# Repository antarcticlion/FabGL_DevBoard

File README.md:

# FabGL_DevBoard
 FabGL development board using ESP32-DevkitC-V4

---

解説は後で書きます。

---

---
# Lastest gerber

https://github.com/antarcticlion/FabGL_DevBoard/raw/main/FabGL_SBC/gerber/ESP32DevkitC-V4-SBC-FabGL_02.zip

---
# BOM

|番号|部品|数|
|:---|:---|:---|
| J1,J2 | ミニＤＩＮソケットfemale 6p | 2|
| J3 | マイクロSDソケット ヒロセDM3AT-SF-PEJM5 | 1|
| U1 | 1x19 ピンソケット | 2|
| U1 | ESP32-DebkitC-VE (Insert to pinsocket) | 1|
| R1～R4 | 2KR抵抗 7mm スルーホール | 4|
| R5～R8,R15,R26,R30 | 120R抵抗 7mm スルーホール | 7|
| R22 | 10KR抵抗 7mm スルーホール | 1|
| R34 | 470R抵抗 7mm スルーホール | 1|
| R9～R14,R16～R21,R23～R25,R27～R29 | 200R抵抗 7mm スルーホール | 18|
| J6 | DE15 Dsub-15P 3rows female horizontal pcb | 1|
| J5 | 3.5mmステレオミニジャック MJ-495A | 1|
| D1 | 5mm LED | 1|
| C2 | 10uF 2.5mm pitch MLCC | 1|
| C1,C10 | 0.1uF 5mm pitch MLCC | 2|
| C8 | 0.33uF 5mm pitch MLCC | 1|
| SW1 or SW2 | SPDT togle switch | 1|
| U7 | STMicroelectronics L7805CV | 1|
| J11 | DC Barreljack | 1|

---
# 取り扱いの注意点
・USBから給電するときはDCジャックの給電を止めてください。  
・ファームウェア更新時にはBootボタンを押す必要があります。Arduino IDE から「→」ボタンで転送を始めたら、しばらく待った後で"Connecting...."と表示された後ですぐbootボタンを押して、転送が開始されたら放してください。  
・I2Cは未チェックです。  
・ESP32-WROVERに対応するためピンアウトを一部変えています。SDカードやエキスパンダを使う場合、初期化時にピン番号を指定してください。  
| 信号 | ピン |
|:---|:---|
| MISO | 35 |
| MOSI | 12 |
| SCK | 14 |
| SS | 13 |

---

# Related Links

https://github.com/fdivitto/FabGL

---

# LICENCE
  
Copyright Antarcticlion 2022. This source describes Open Hardware and is licensed under the CERN-OHLW v2  
  
You may redistribute and modify this documentation and make products using it under the terms of the CERN-OHL-W v2 (https:/cern.ch/cern-ohl). This documentation is distributed WITHOUT ANY EXPRESS OR IMPLIED WARRANTY, INCLUDING OF MERCHANTABILITY, SATISFACTORY QUALITY AND FITNESS FOR A PARTICULAR PURPOSE. Please see the CERN-OHL-W v2 for applicable conditions. Source location: https://github.com/antarcticlion/RGB_UNICONV As per CERN-OHL-W v2 section 4.1, should You produce hardware based on these sources, You must maintain the Source Location visible on the external case of the White Rabbit switch or other product you make using this documentation.  
  
 CERN Open Hardware Licence Version 2 - Weakly Reciprocal
- https://spdx.org/licenses/CERN-OHL-W-2.0.html  
- https://github.com/antarcticlion/RGB_UNICONV/raw/main/cern_ohl_w_v2.pdf PDF  
- https://github.com/antarcticlion/RGB_UNICONV/raw/main/cern_ohl_w_v2_howto.pdf PDF

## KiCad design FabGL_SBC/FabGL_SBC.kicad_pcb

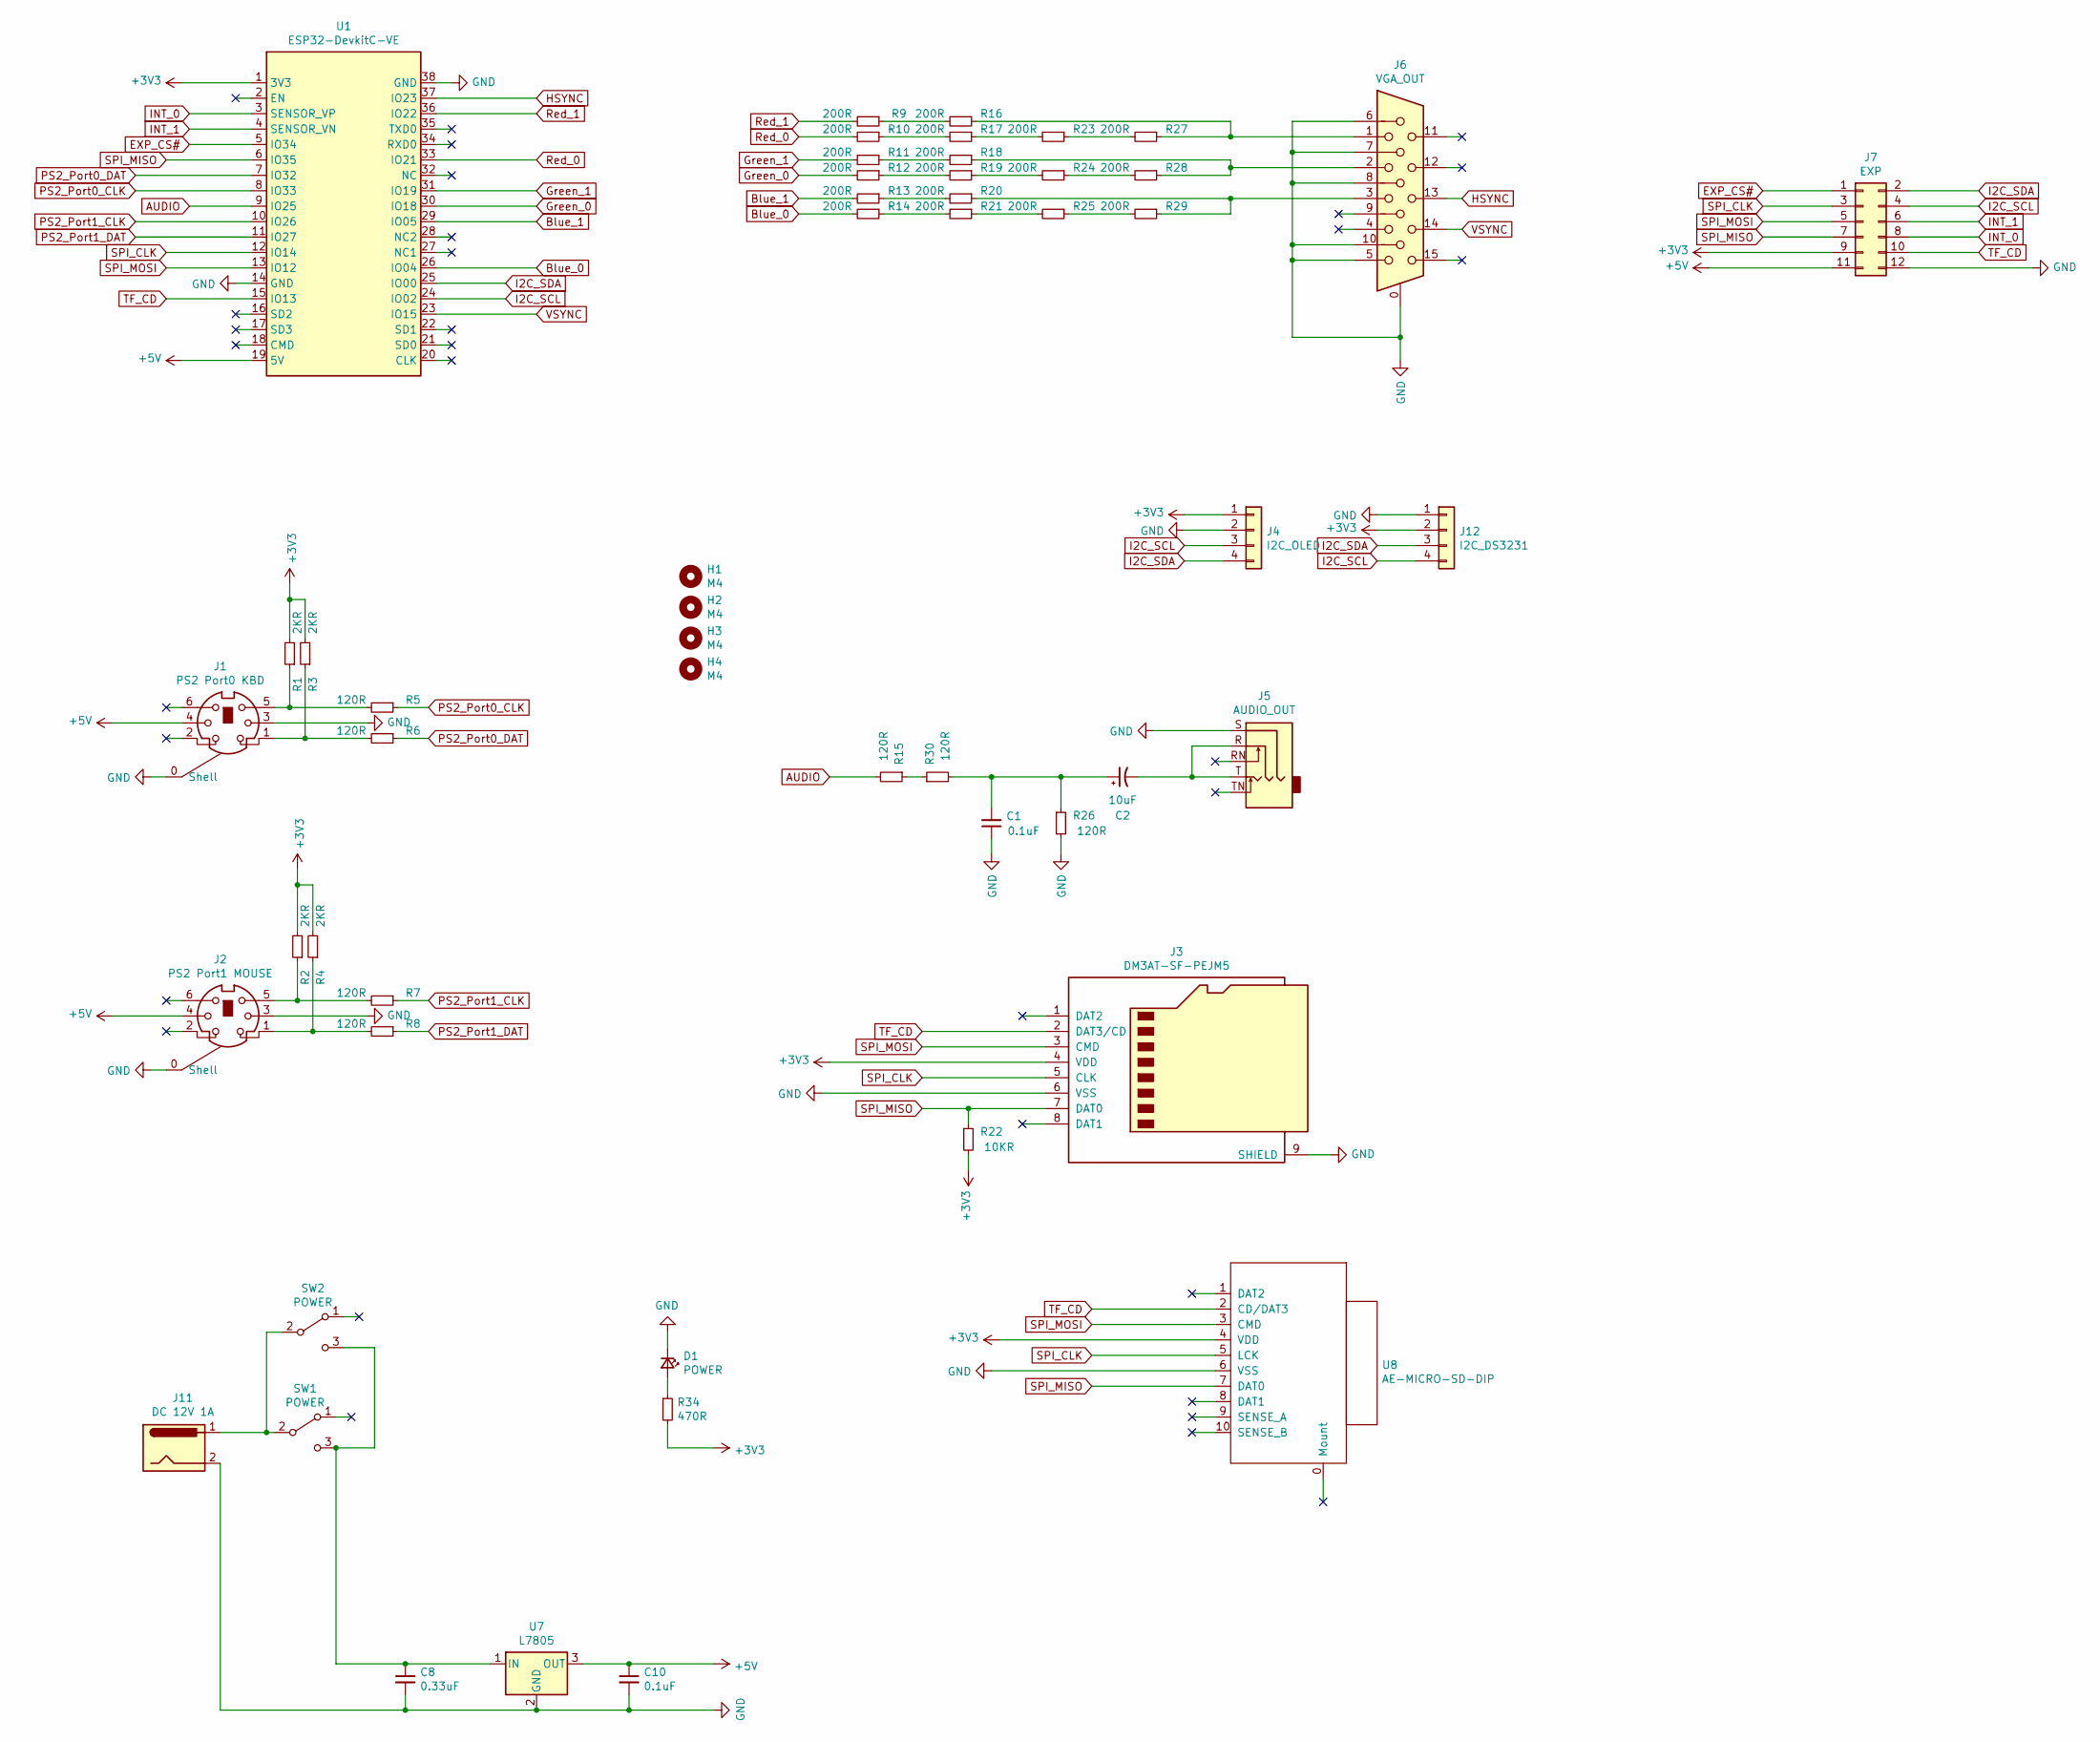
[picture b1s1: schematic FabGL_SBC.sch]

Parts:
C1, C10: 0.1uF; C_Disc_D5.0mm_W2.5mm_P5.00mm
C2: 10uF; CP_Radial_D6.3mm_P2.50mm
C8: 0.33uF; C_Disc_D5.0mm_W2.5mm_P5.00mm
D1: POWER; LED_D5.0mm
H1, H2, H3, H4: M4; MountingHole_4.3mm_M4
J1: PS2 Port0 KBD; mini DIN 6 PCB
J2: PS2 Port1 MOUSE; mini DIN 6 PCB
J3: DM3AT-SF-PEJM5; microSD_HC_Hirose_DM3AT-SF-PEJM5
J4: I2C_OLED; PinHeader_1x04_P2.54mm_Vertical
J5: AUDIO_OUT; PJ-3900-04
J6: VGA_OUT; DB_15F-VGA_L
J7: EXP; PinHeader_2x06_P2.54mm_Vertical
J11: DC 12V 1A; BarrelJack_Horizontal
J12: I2C_DS3231; PinHeader_1x04_P2.54mm_Vertical
R1, R2, R3, R4: 2KR; R_Axial_DIN0207_L6.3mm_D2.5mm_P2.54mm_Vertical
R5, R6, R7, R8, R15, R26, R30: 120R; R_Axial_DIN0207_L6.3mm_D2.5mm_P2.54mm_Vertical
R9, R10, R11, R12, R13, R14, R16, R17, R18, R19, R20, R21, R23, R24, R25, R27, R28, R29: 200R; R_Axial_DIN0207_L6.3mm_D2.5mm_P2.54mm_Vertical
R22: 10KR; R_Axial_DIN0207_L6.3mm_D2.5mm_P2.54mm_Vertical
R34: 470R; R_Axial_DIN0207_L6.3mm_D2.5mm_P2.54mm_Vertical
SW1: POWER; 2MS1T1B4M7QES
SW2: POWER; PinHeader_1x03_P2.54mm_Vertical
U1: ESP32-DevkitC-VE; ESP32-DevkitC-V4
U7: L7805; TO-220-3_Vertical
U8: AE-MICRO-SD-DIP

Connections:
+3V3: J3.4 (VDD), J4.1, J7.9, J12.2, R1.2, R2.2, R3.2, R4.2, R22.2, R34.2, U1.1 (3V3), U8.4 (VDD)
+5V: C10.1, J1.4, J2.4, J7.11, U1.19 (5V), U7.3 (OUT)
AUDIO: R15.2, U1.9 (IO25)
Blue_0: R14.2, U1.26 (IO04)
Blue_1: R13.2, U1.29 (IO05)
EXP_CS#: J7.1, U1.5 (IO34)
GND: C1.1, C8.2, C10.2, D1.1 (K), J1.0 (Shell), J1.3, J2.0 (Shell), J2.3, J3.6 (VSS), J3.9 (SHIELD), J4.2, J5.S, J6.0, J6.5, J6.6, J6.7, J6.8, J6.10, J7.12, J11.2, J12.1, R26.2, U1.14 (GND), U1.38 (GND), U7.2 (GND), U8.6 (VSS)
Green_0: R12.2, U1.30 (IO18)
Green_1: R11.2, U1.31 (IO19)
HSYNC: J6.13, U1.37 (IO23)
I2C_SCL: J4.3, J7.4, J12.4, U1.24 (IO02)
I2C_SDA: J4.4, J7.2, J12.3, U1.25 (IO00)
INT_0: J7.8, U1.3 (SENSOR_VP)
INT_1: J7.6, U1.4 (SENSOR_VN)
unnamed: C1.2, C2.1, R26.1, R30.2
unnamed: C2.2, J5.R, J5.T
unnamed: C8.1, SW1.3 (C), SW2.3 (C), U7.1 (IN)
unnamed: D1.2 (A), R34.1
unnamed: J1.1, R3.1, R6.2
unnamed: J1.5, R1.1, R5.2
unnamed: J2.1, R4.1, R8.2
unnamed: J2.5, R2.1, R7.2
unnamed: J6.1, R16.1, R27.1
unnamed: J6.2, R18.1, R28.1
unnamed: J6.3, R20.1, R29.1
unnamed: J11.1, SW1.2 (B), SW2.2 (B)
unnamed: R10.1, R17.2
unnamed: R11.1, R18.2
unnamed: R12.1, R19.2
unnamed: R13.1, R20.2
unnamed: R14.1, R21.2
unnamed: R15.1, R30.1
unnamed: R9.1, R16.2
unnamed: R17.1, R23.2
unnamed: R19.1, R24.2
unnamed: R21.1, R25.2
unnamed: R23.1, R27.2
unnamed: R24.1, R28.2
unnamed: R25.1, R29.2
PS2_Port0_CLK: R5.1, U1.8 (IO33)
PS2_Port0_DAT: R6.1, U1.7 (IO32)
PS2_Port1_CLK: R7.1, U1.10 (IO26)
PS2_Port1_DAT: R8.1, U1.11 (IO27)
Red_0: R10.2, U1.33 (IO21)
Red_1: R9.2, U1.36 (IO22)
SPI_CLK: J3.5 (CLK), J7.3, U1.12 (IO14), U8.5 (LCK)
SPI_MISO: J3.7 (DAT0), J7.7, R22.1, U1.6 (IO35), U8.7 (DAT0)
SPI_MOSI: J3.3 (CMD), J7.5, U1.13 (IO12), U8.3 (CMD)
TF_CD: J3.2 (DAT3/CD), J7.10, U1.15 (IO13), U8.2 (CD/DAT3)
VSYNC: J6.14, U1.23 (IO15)

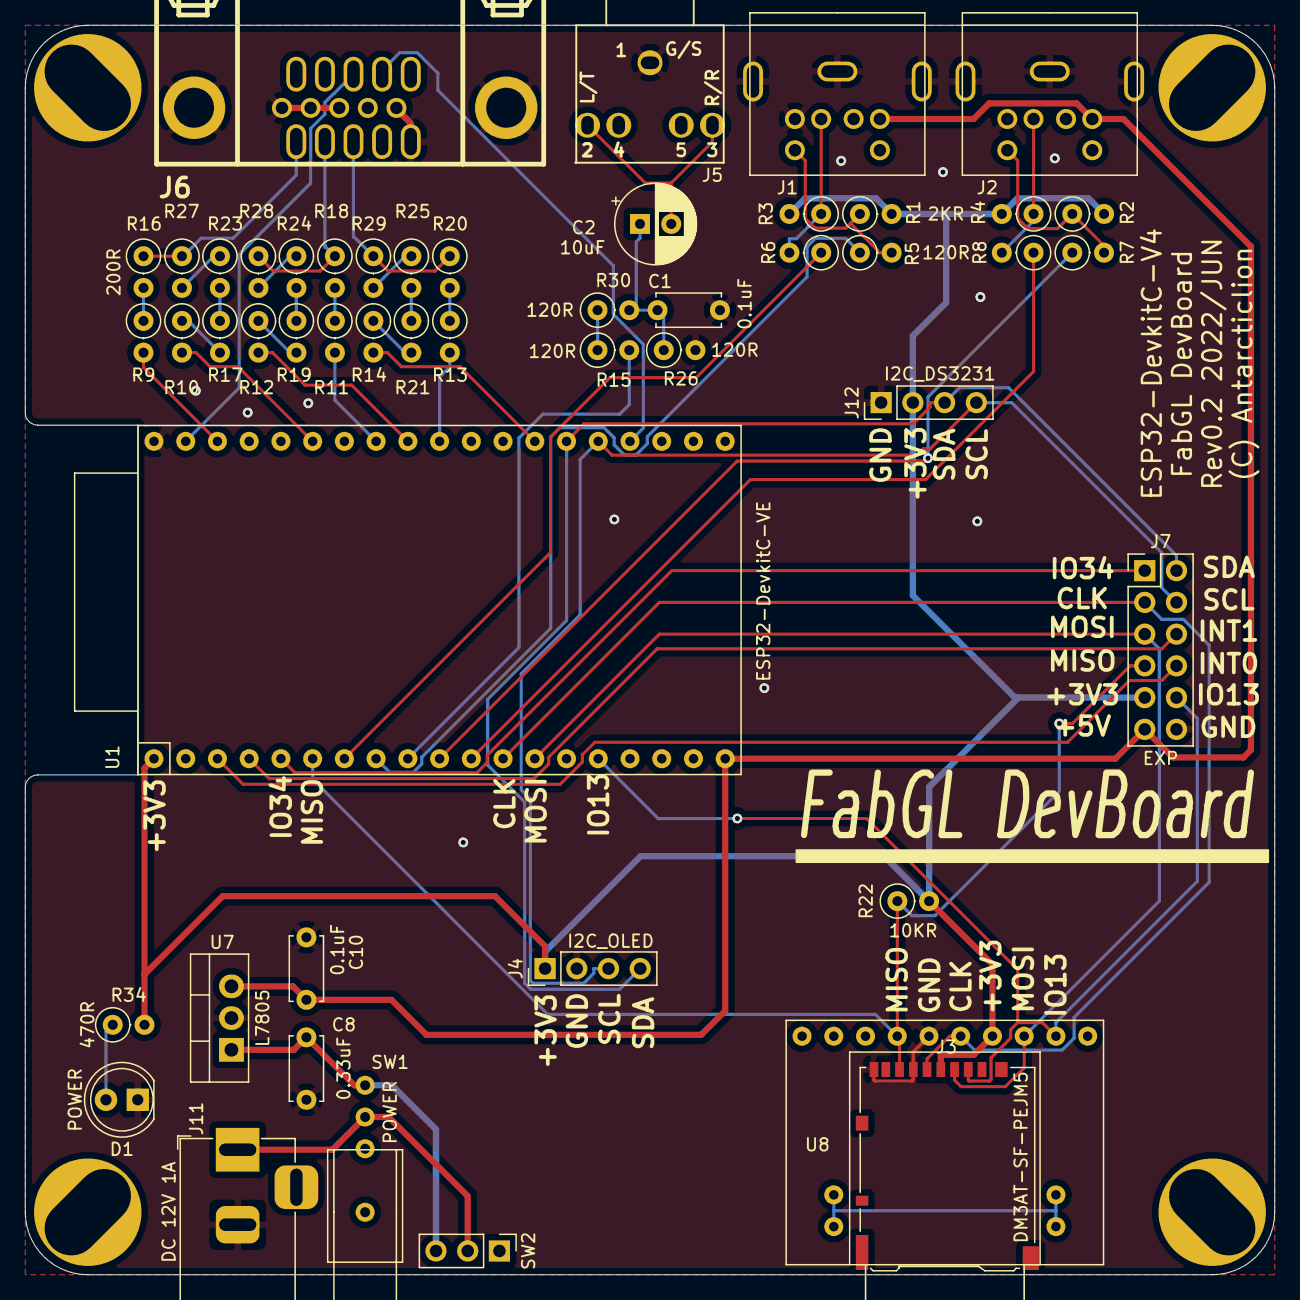
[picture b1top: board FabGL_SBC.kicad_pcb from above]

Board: 2 copper layers, 100.0 x 100.0 mm, 54 parts (0 on the bottom side), 50 nets.
